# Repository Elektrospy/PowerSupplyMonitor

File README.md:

# I2C Powersupply Monitor Hub 

This repository contains the schematics and sourcecode for the I2C powersupply monitor hub.

This project is used to monitor and control the HRPG-300 power supplies of the ceiling pixel lamp.
https://github.com/c3e/CeilingPixelLamp

* Control:
	* toggle power output of single power supply
* Monitor:
	* if supply output is active
	* current power consumption for every 5 led panel (10 per power supply)

### Hardware used
* ACS712 30A version
	* Hallsensor based current measuring
* TCA9548A
	* Low-Voltage 8-Channel I2C Switch with Reset
* PCF8575 
	* Remote16-BIT I2C AND SMBus I/O Expander with Interrupt Output
* PCA9685
	* 16-channel, 12-bit PWM Fm+ I2C-bus LED controller
* ADS1015
	* I2C 4-Channel 12-Bit ADC
* PC817
	* High Density Mounting Type Photocoupler

## I2C Hub

I2C Hub Board for I2C Nodes

## I2C Node

I2C Node Board + GY-712 30A

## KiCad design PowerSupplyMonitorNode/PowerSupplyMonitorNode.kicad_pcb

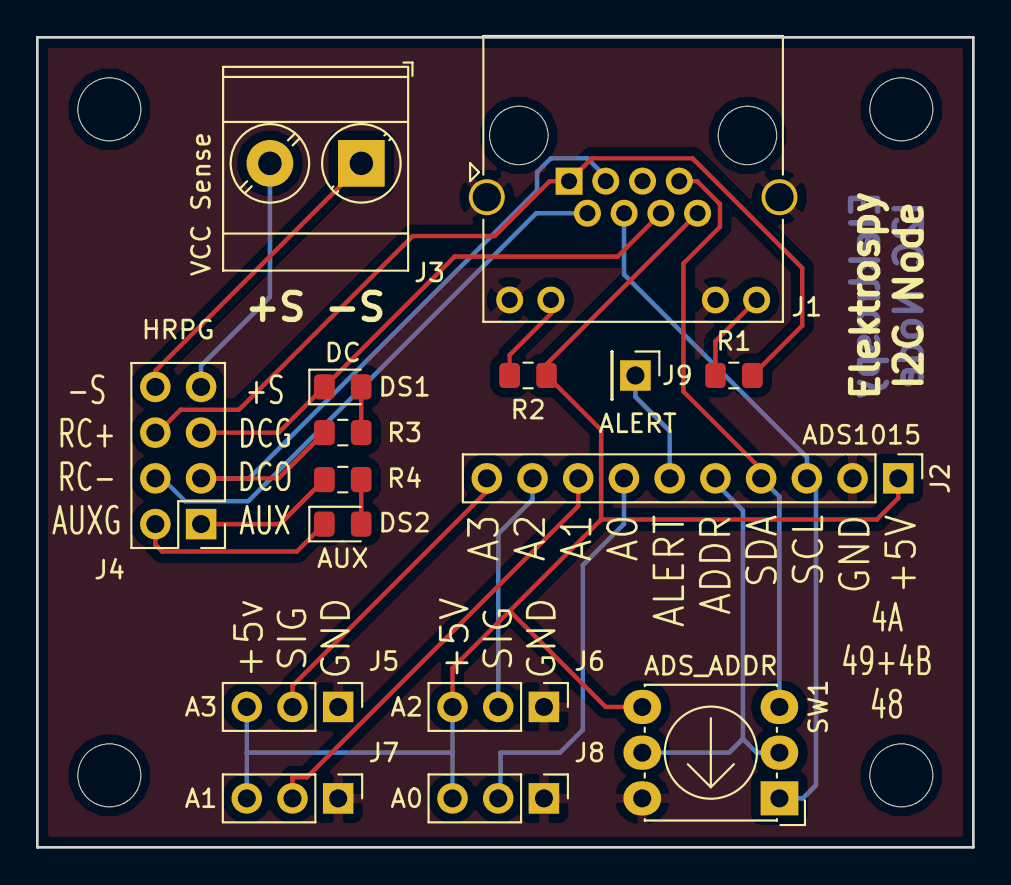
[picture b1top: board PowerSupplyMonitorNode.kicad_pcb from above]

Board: 2 copper layers, 52.0 x 45.0 mm, 20 parts (0 on the bottom side), 22 nets.

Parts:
DS1: DC; LED_0805_2012Metric_Pad1.15x1.40mm_HandSolder
DS2: AUX; LED_0805_2012Metric_Pad1.15x1.40mm_HandSolder
J1: RJ45 PWR; RJ45_Amphenol_RJHSE538X
J2: ADS1015; PinHeader_1x10_P2.54mm_Vertical
J3: VCC Sense; TerminalBlock_Phoenix_MKDS-3-2-5.08_1x02_P5.08mm_Horizontal
J4: HRPG; PinHeader_2x04_P2.54mm_Vertical
J5: A3; PinHeader_1x03_P2.54mm_Vertical
J6: A2; PinHeader_1x03_P2.54mm_Vertical
J7: A1; PinHeader_1x03_P2.54mm_Vertical
J8: A0; PinHeader_1x03_P2.54mm_Vertical
J9: ALERT; PinHeader_1x01_P2.54mm_Vertical
MH1, MH2, MH3, MH4: MountingHole; MountingHole_3.5mm
R1, R2, R3, R4: 220; R_0805_2012Metric_Pad1.15x1.40mm_HandSolder
SW1: ADS_ADDR; CTS_ 220AD_0

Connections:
+5V: J1.8, J2.1, J5.3, J6.3, J7.3, J8.3, R2.1, SW1.3
/+S: J3.2, J4.7
/-S: J3.1, J4.8
/A0: J2.7, J8.2
/A1: J2.8, J7.2
/A2: J2.9, J6.2
/A3: J2.10, J5.2
/ADDR: J2.5, SW1.1
/ALERT: J2.6, J9.1
/AUX: J4.1, R4.1
/AUXG: DS2.1, J4.2
/DC_GND: DS1.1, J1.6, J4.5
/DC_OK: J1.3, J4.3, R3.2
/RC+: J1.1, J4.6, R1.1
/RC-: J1.2, J4.4
/SCL: J1.4, J2.3, SW1.5
/SDA: J1.7, J2.4, SW1.4
GND: J1.5, J1.9, J1.11, J1.SH, J2.2, J5.1, J6.1, J7.1, J8.1, SW1.2
unnamed: DS1.2, R3.1
unnamed: DS2.2, R4.2
unnamed: J1.10, R2.2
unnamed: J1.12, R1.2

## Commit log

2018-07-26 initial commit added kicad project added schematic of main i2c hub added datasheets for ics
2018-07-27 added dip switches to i2c ics for adress selection added pullup resistors to i2c input lines added placeholder footprint for pcf8575 added minimal pcb placement for testing
2018-07-27 changed package and footprint from sop to soi for pcf8575
2018-07-27 updated 3d pcb render to show new dcf8575 package
2018-07-27 added new 3d render of front and back view of pcb added pcb routing from autorouter added power led indicator added i2c ic adress ranges to silkscreen added unused ic pins pinout info silkscreen adde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
2018-07-28 added new pcb i2c node
    added new datasheet for dts 220ADC04 coded rotary
    added new datasheet for hrpg 300 power supply
    added gerber files for i2c hub and node
    added new 3d render for i2c node
2018-07-28 moved render images to sub directory
2018-07-28 added more pinout infos for i2c node to silkscreen
    updated render of i2c node so show new silkscreen stuff
2018-07-28 added minimal readme
    added many vias for ground front and back plane
    updated 3d render of i2c hub pcb
    updated gerber archive files
2018-07-30 updated readme and license file
    added datasheet for ads1015
    added datasheet for pca9685
    added foto of gy-712 30a sensor
    added small changes to pcbs
    updated 3d render of pcbs
2018-07-31 Update and rename LICENSE.md to LICENSE
2018-08-08 added hit counter
2018-08-19 added basic pcb testing firmware
    it scans for i2c devices and blinks some leds
2018-08-19 fixed pcb errors
    swapped gnd and vcc pin of 4 position switch to fix first two addresses
    added custom 3d model for 4 position switch as step file
    added custom library for 4 position switch
    fixed routing of feedback signal lines (dc0-dc5)
    removed double current limiting led resistors
2018-08-19 added more vias for gnd plane on both sides
2018-11-04 added small changes to power supply pcbs added needed libraries to node firmware folder added node test program for wemos D1 mini as master added placeholder header and source file for new firmware
2018-11-04 changed PCA9685 library
2018-11-12 removed broken merge snippets
2018-11-14 changed libs to platformio used ones
2018-11-14 remove false lib versions
2018-11-20 added basic contruct for firmware image added private method to calculate average adc milliampere value added public method to get the average milliampere value for a output changed from single value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
2018-12-12 test routine commit
2019-01-07 Update LICENSE
    fixed license file
2019-03-01 Changed from Deviot to VS-Code
2019-03-01 small changes with the node class
2019-03-04 removed external tca library
2019-03-05 added new blank class for i2chub added new debug print for milliampere cleanup of i2cnode code
2019-03-06 added basic methods to i2chub class
2019-03-07 removed testing platformio environment removed testing ino file added missing tca port switching fixed same input value for all nodes and channels
2019-03-08 added branch for testing
2019-03-08 removed unit tests because of forced cloud account changed limit of float debug print
2019-03-08 reverted pio ini
2019-03-08 added git ignore
2019-03-09 fixed kicad project files with older copy
2019-03-10 added new lib dependency PCF857X added basic port initialization for pcf6575 the start state for the powersupplies is set to off
2019-03-11 added basic powersupply toggle over buttons
2019-03-12 added catch2 testing framework header
2019-03-13 added basic testing loop to toggle power supplies
2019-03-14 moved debugging methods to external files
2019-03-14 added basic test for i2c oled display
2019-03-15 added test dashboard for adc in milliampere
2019-03-15 removed unused files
2019-03-15 changed main display lib to u8g2
2019-03-15 fixed ampere prescaler from 10 to 12bit removed milliampere values removed milliampere debug messages
2019-03-16 flipped adc ampere inputs of nodes to match up with final cabeling
2019-03-17 added new dashboard with sum ampere added new fake dashboard for ip info added progress bar for sum ampere added dashboard circles menu display added dashboard switches to last button
2019-03-17 added new gain value for adc changed progress bar from rounded to normal box draw added switching for positiv and negativ ampere values
2019-03-17 added hallsensor drift value method added debug dashboard for raw values removed changed gain for ads1015
2019-03-17 added small note for middle adc value
